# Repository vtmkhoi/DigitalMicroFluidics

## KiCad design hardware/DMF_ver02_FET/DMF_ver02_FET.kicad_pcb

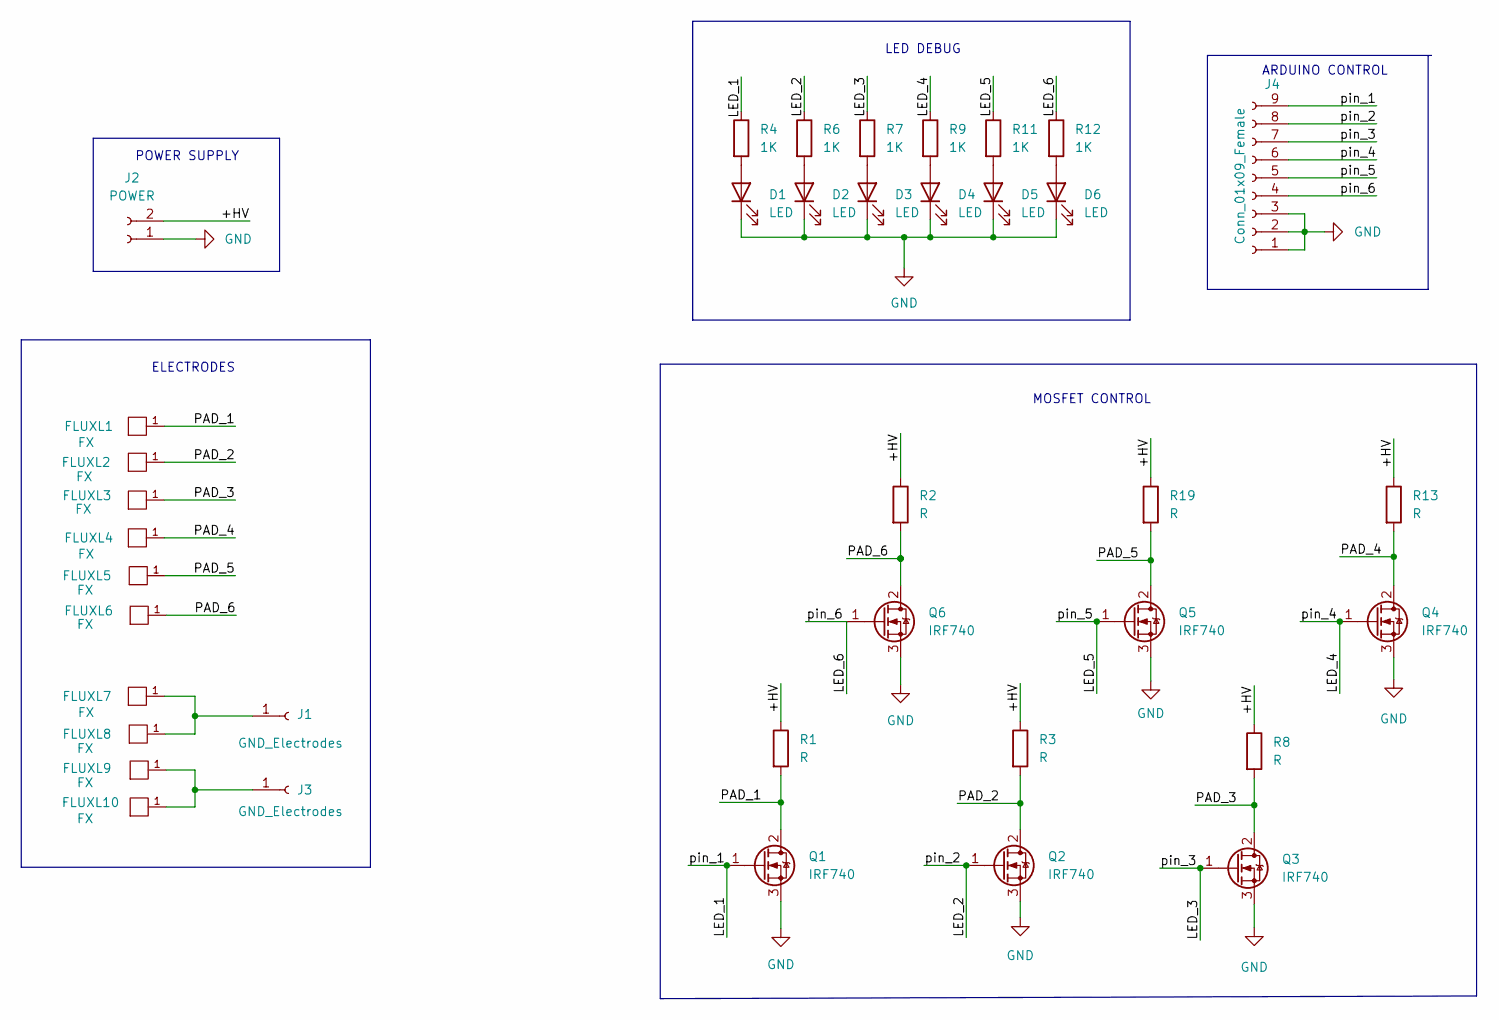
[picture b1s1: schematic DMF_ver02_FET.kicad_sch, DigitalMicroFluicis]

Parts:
D1, D2, D3, D4, D5, D6: LED; LED_0603_1608Metric_Pad1.05x0.95mm_HandSolder
FLUXL1, FLUXL2, FLUXL3, FLUXL4, FLUXL5, FLUXL6, FLUXL7, FLUXL8, FLUXL9, FLUXL10: FX; FLUXPAD_2_75_4MIL_FINAL
J1, J3: GND_Electrodes; PinSocket_1x01_P2.54mm_Vertical
J2: POWER; TerminalBlock_bornier-2_P5.08mm
J4: Conn_01x09_Female; PinHeader_1x09_P2.54mm_Vertical
Q1, Q2, Q3, Q4, Q5, Q6: IRF740; TO-263-3_TabPin2
R1, R2, R3, R8, R13, R19: R; R_1206_3216Metric_Pad1.30x1.75mm_HandSolder
R4, R6, R7, R9, R11, R12: 1K; R_1206_3216Metric_Pad1.30x1.75mm_HandSolder

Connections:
/+HV: J2.2, R1.1, R2.1, R3.1, R8.1, R13.1, R19.1
/LED_1: J4.9, Q1.1 (G), R4.1
/LED_2: J4.8, Q2.1 (G), R6.1
/LED_3: J4.7, Q3.1 (G), R7.1
/LED_4: J4.6, Q4.1 (G), R9.1
/LED_5: J4.5, Q5.1 (G), R11.1
/LED_6: J4.4, Q6.1 (G), R12.1
/PAD_1: FLUXL1.1, Q1.2 (D), R1.2
/PAD_2: FLUXL2.1, Q2.2 (D), R3.2
/PAD_3: FLUXL3.1, Q3.2 (D), R8.2
/PAD_4: FLUXL4.1, Q4.2 (D), R13.2
/PAD_5: FLUXL5.1, Q5.2 (D), R19.2
/PAD_6: FLUXL6.1, Q6.2 (D), R2.2
GND: D1.1 (K), D2.1 (K), D3.1 (K), D4.1 (K), D5.1 (K), D6.1 (K), J2.1, J4.1, J4.2, J4.3, Q1.3 (S), Q2.3 (S), Q3.3 (S), Q4.3 (S), Q5.3 (S), Q6.3 (S)
unnamed: D1.2 (A), R4.2
unnamed: D2.2 (A), R6.2
unnamed: D3.2 (A), R7.2
unnamed: D4.2 (A), R9.2
unnamed: D5.2 (A), R11.2
unnamed: D6.2 (A), R12.2
unnamed: FLUXL7.1, FLUXL8.1, J1.1
unnamed: FLUXL9.1, FLUXL10.1, J3.1

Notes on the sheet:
POWER SUPPLY
ARDUINO CONTROL
LED DEBUG
ELECTRODES
MOSFET CONTROL

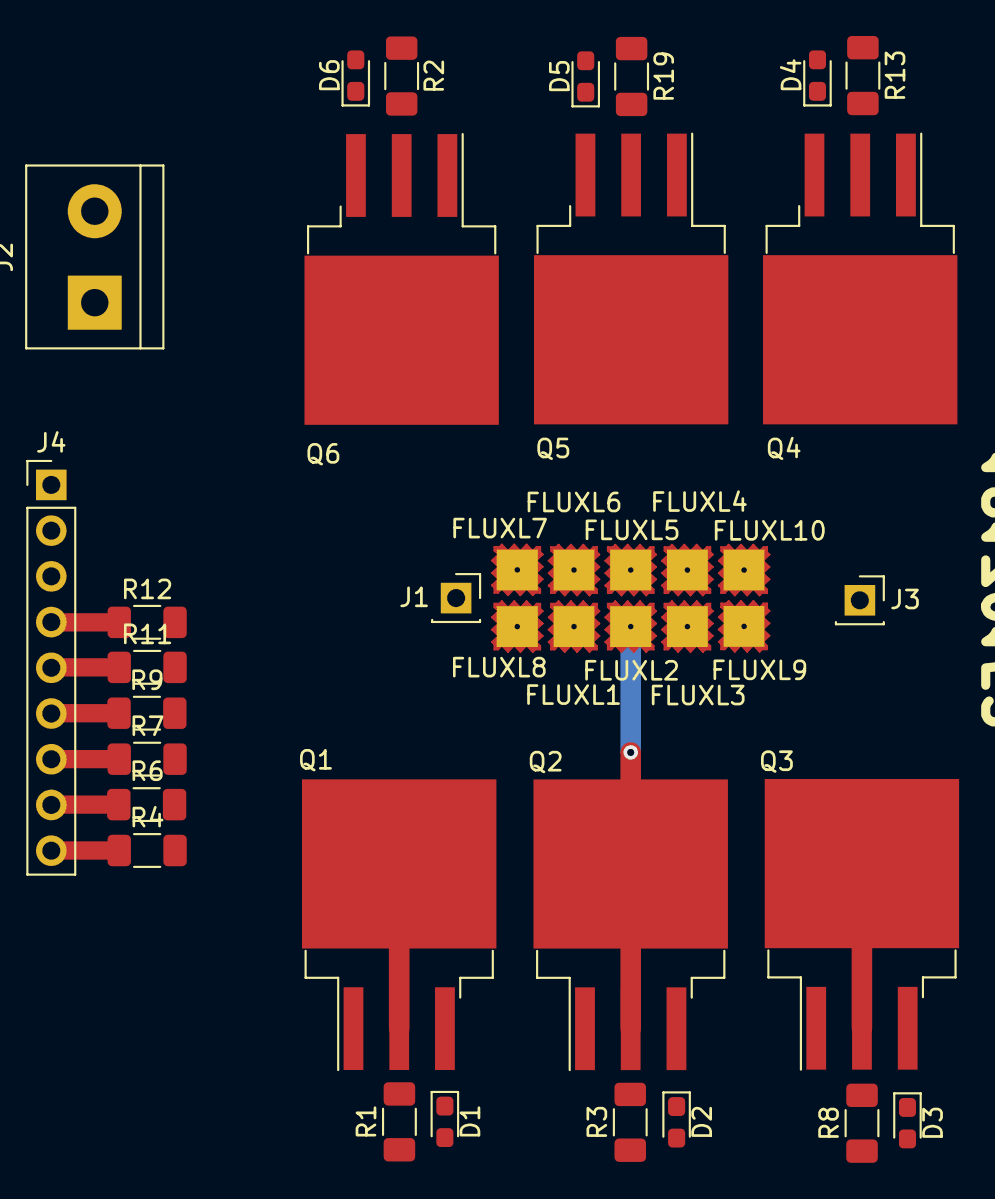
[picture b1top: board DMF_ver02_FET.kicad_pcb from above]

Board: 2 copper layers, 38 parts (0 on the bottom side), 22 nets.

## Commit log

2022-09-26 Update gitignore
2022-09-27 Update Schematic of DMF Project
2022-09-27 Update documents
2022-09-27 Modify folder structure
2022-09-30 Update schem + layout PCB: Changes from 10 electrodes -> 6 electrodes
2022-10-01 Update PCB layout version 01
2022-10-01 Update PCB layout
2022-10-17 Create DMF board version SMD
2022-10-17 Update folder structure. Create Version SMD
2022-10-18 Update PCB layout: Placed components.
